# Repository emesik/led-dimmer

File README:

LED lighting dimmer

My aim was to create a dimmer for a long LED stripe which would go around a big room. I didn't
want to output raw PWM and have around 20m of cable acting as antenna, even though the frequency
could be low and theoretically harmless. For that reason the circuit has two modules:

	1. PWM generator with ATtiny85 microcontroller, two MOSFETs and potentiometer input
	2. LC filter with cutoff frequency just a bit above 150Hz

The final output is flat voltage depending on the PWM duty cycle. There is possibility, however, to
bypass the filter.

I used DTP-24 ferrite powder ring choke, rated up to 6A. That limits the circuit to 72W output.
The main MOSFET allows even 12A of continuous output at 25°C, so the max power depends mostly on
the choke you choose.

TODO:
	* So far tested it with tiny load. Must see how it behaves with a few meters of LED stripe.
	* The table of potentiometer to PWM duty cycle translation is still far from perfect and fails
	  to provide linear dimming.

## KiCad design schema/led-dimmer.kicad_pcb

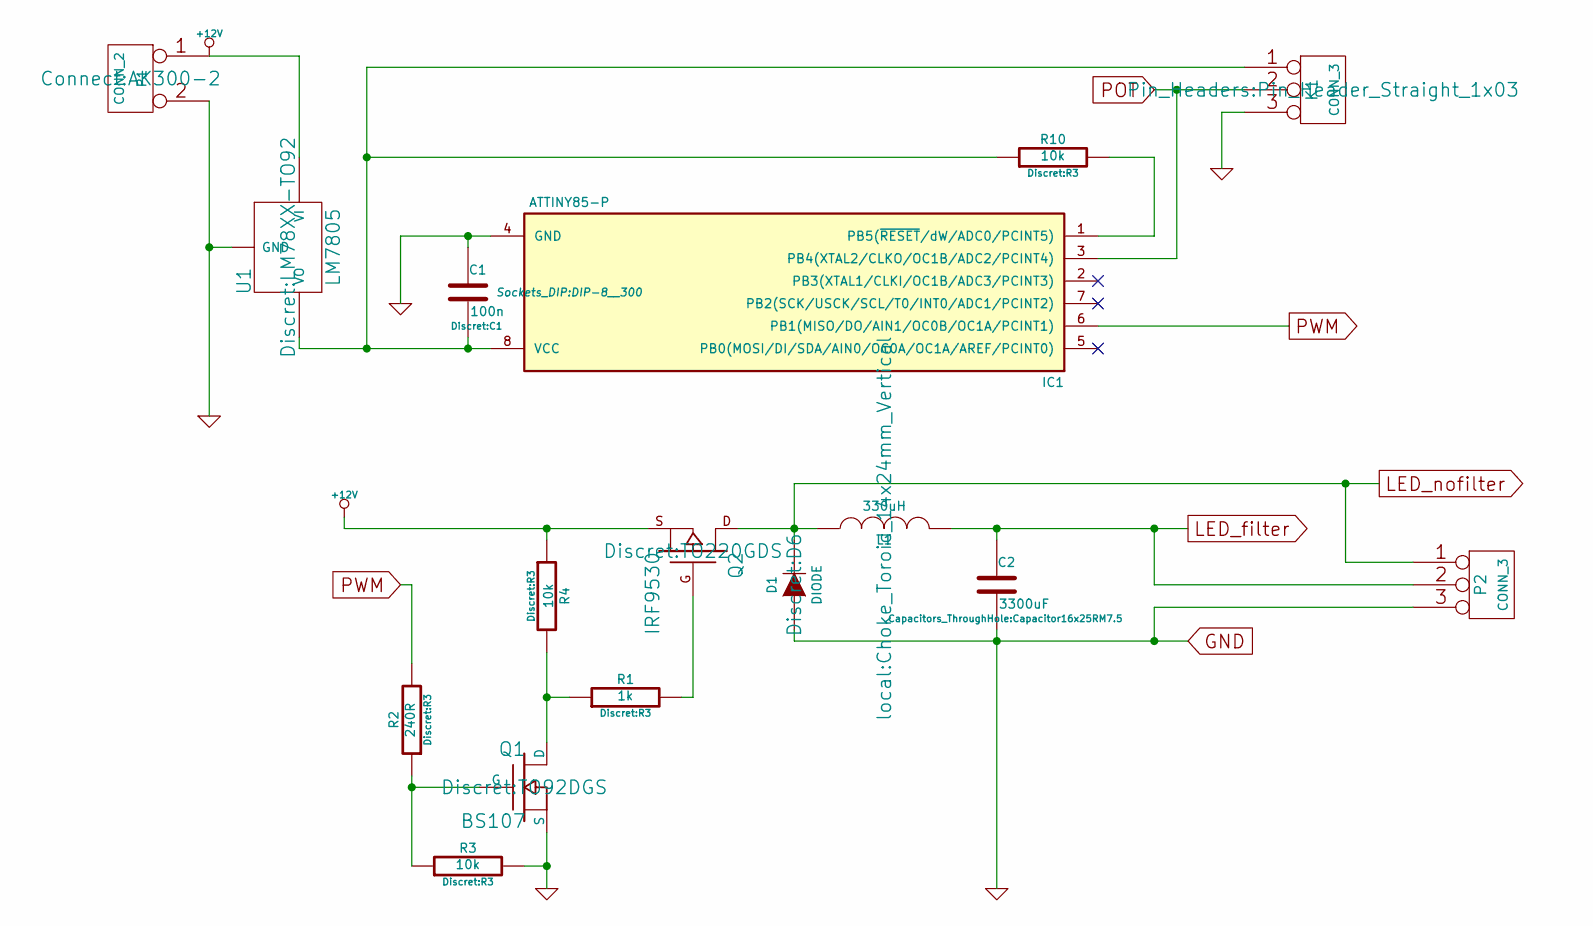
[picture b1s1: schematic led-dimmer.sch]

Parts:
C1: 100n; C1
C2: 3300uF; Capacitor16x25RM7.5
D1: DIODE; D6
IC1: ATTINY85-P; DIP-8__300
K1: CONN_3; Pin_Header_Straight_1x03
L1: 330uH; Choke_Toroid_14x24mm_Vertical
P1: CONN_2; AK300-2
P2: CONN_3; AK300-3
Q1: BS107; TO92DGS
Q2: IRF9530; TO220GDS
R1: 1k; R3
R2: 240R; R3
R3, R4, R10: 10k; R3
U1: LM7805; LM78XX-TO92

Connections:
+12V: P1.1, Q2.S, R4.1, U1.VI
GND: C1.1, C2.2, D1.1 (A), IC1.4 (GND), K1.3, P1.2 (PM), P2.3, Q1.S, R3.2, U1.GND
LED_filter: C2.1, L1.2, P2.2 (PM)
LED_nofilter: D1.2 (K), L1.1, P2.1, Q2.D
unnamed: C1.2, IC1.8 (VCC), K1.1, R10.1, U1.VO
unnamed: IC1.1 (PB5(~RESET~/dW/ADC0/PCINT5)), R10.2
unnamed: Q1.D, R1.1, R4.2
unnamed: Q1.G, R2.1, R3.1
unnamed: Q2.G, R1.2
POT: IC1.3 (PB4(XTAL2/CLKO/OC1B/ADC2/PCINT4)), K1.2 (PM)
PWM: IC1.6 (PB1(MISO/DO/AIN1/OC0B/OC1A/PCINT1)), R2.2

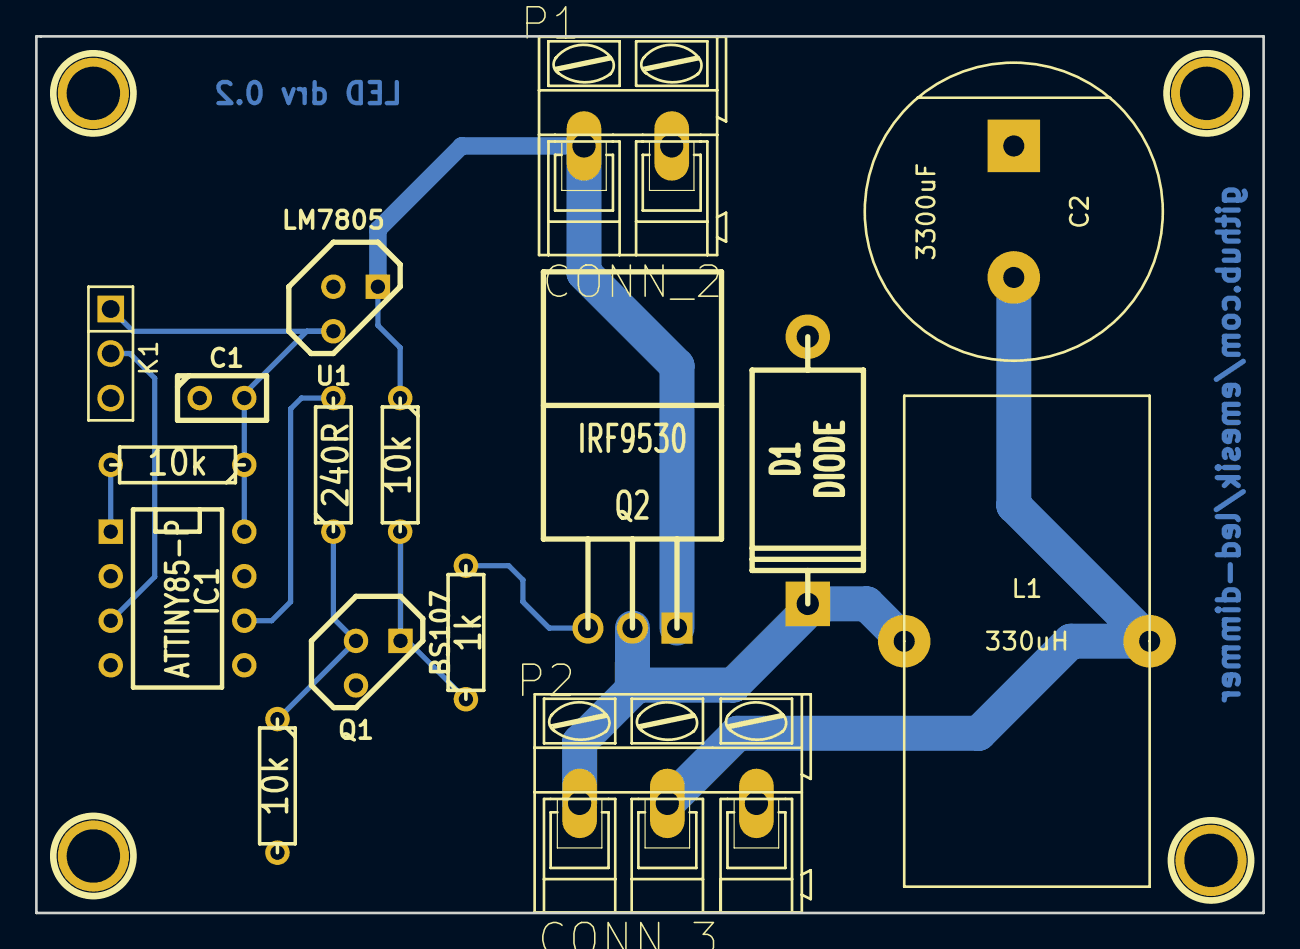
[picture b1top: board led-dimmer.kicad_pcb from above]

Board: 2 copper layers, 70.0 x 50.0 mm, 16 parts (0 on the bottom side), 11 nets.

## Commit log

2014-11-19 Initial release
2014-11-20 Update filenames to match project name
2014-11-22 Make PCB corrections
2014-11-22 Plot rev 0.2 PCB
2014-12-01 New PCB which allows to connect bypassing LC filter
